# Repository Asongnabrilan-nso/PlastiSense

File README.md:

[Video: PlastiSense Demo](https://youtu.be/B_dy0DAJdtQ)

# PlastiSense

PlastiSense is a precise **filament diameter sensor** powered by the **Seeed Studio XIAO ESP32-C3**. It is designed to monitor filament quality in real-time, offering a web-based dashboard and API for data integration.

## 🚀 Features

-   **Real-time Measurement**: High-precision diameter readings in millimeters (mm).
-   **Web Dashboard**: Hosted on the device itself (`http://winfidel.local`), providing a visual interface for monitoring.
-   **REST API**: JSON endpoints for easy integration with other systems (e.g., OctoPrint, Home Assistant).
-   **WiFi Connectivity**: Connects to your home/office network.
-   **Captive Portal**: Easy initial setup via the `SK-WInFiDEL-Setup` access point.
-   **OTA Updates**: Support for Over-The-Air firmware updates.

## 🛠️ Hardware

The project is built around:
-   **Microcontroller**: [Seeed Studio XIAO ESP32-C3](https://www.seeedstudio.com/Seeed-XIAO-ESP32C3-p-5431.html)
-   **Custom PCB**: Files located in the `PlastiSense_PCB` dictionary.
-   **Stl Files**: 3D printable case files located in `stl` directory.

## 📁 Project Structure

-   `Firmware/`: Source code for the ESP32-C3 firmware (PlatformIO project).
-   `Hardware/`: Mechanical parts and diagrams.
-   `PlastiSense_PCB/`: KiCad PCB design files.
-   `stl/`: 3D printable STL files for the sensing unit.

## ⚡ Getting Started

### 1. Build & Flush Firmware
Detailed instructions for building and flashing the firmware can be found in the [Firmware Documentation](Firmware/README.md).

### 2. Connect to the Device
1.  Power on the PlastiSense device.
2.  Connect to the WiFi network named **SK-WInFiDEL-Setup**.
3.  A captive portal should open. If not, visit `http://192.168.4.1`.
4.  Configure your local WiFi credentials.

### 3. Access the Dashboard
Once connected to your network, access the device at:
-   **URL**: `http://winfidel.local`
-   **API Endpoint**: `http://winfidel.local/api/v0/diameter/read`

For more details on connection and API usage, see the [Connection Guide](Firmware/connection.md).

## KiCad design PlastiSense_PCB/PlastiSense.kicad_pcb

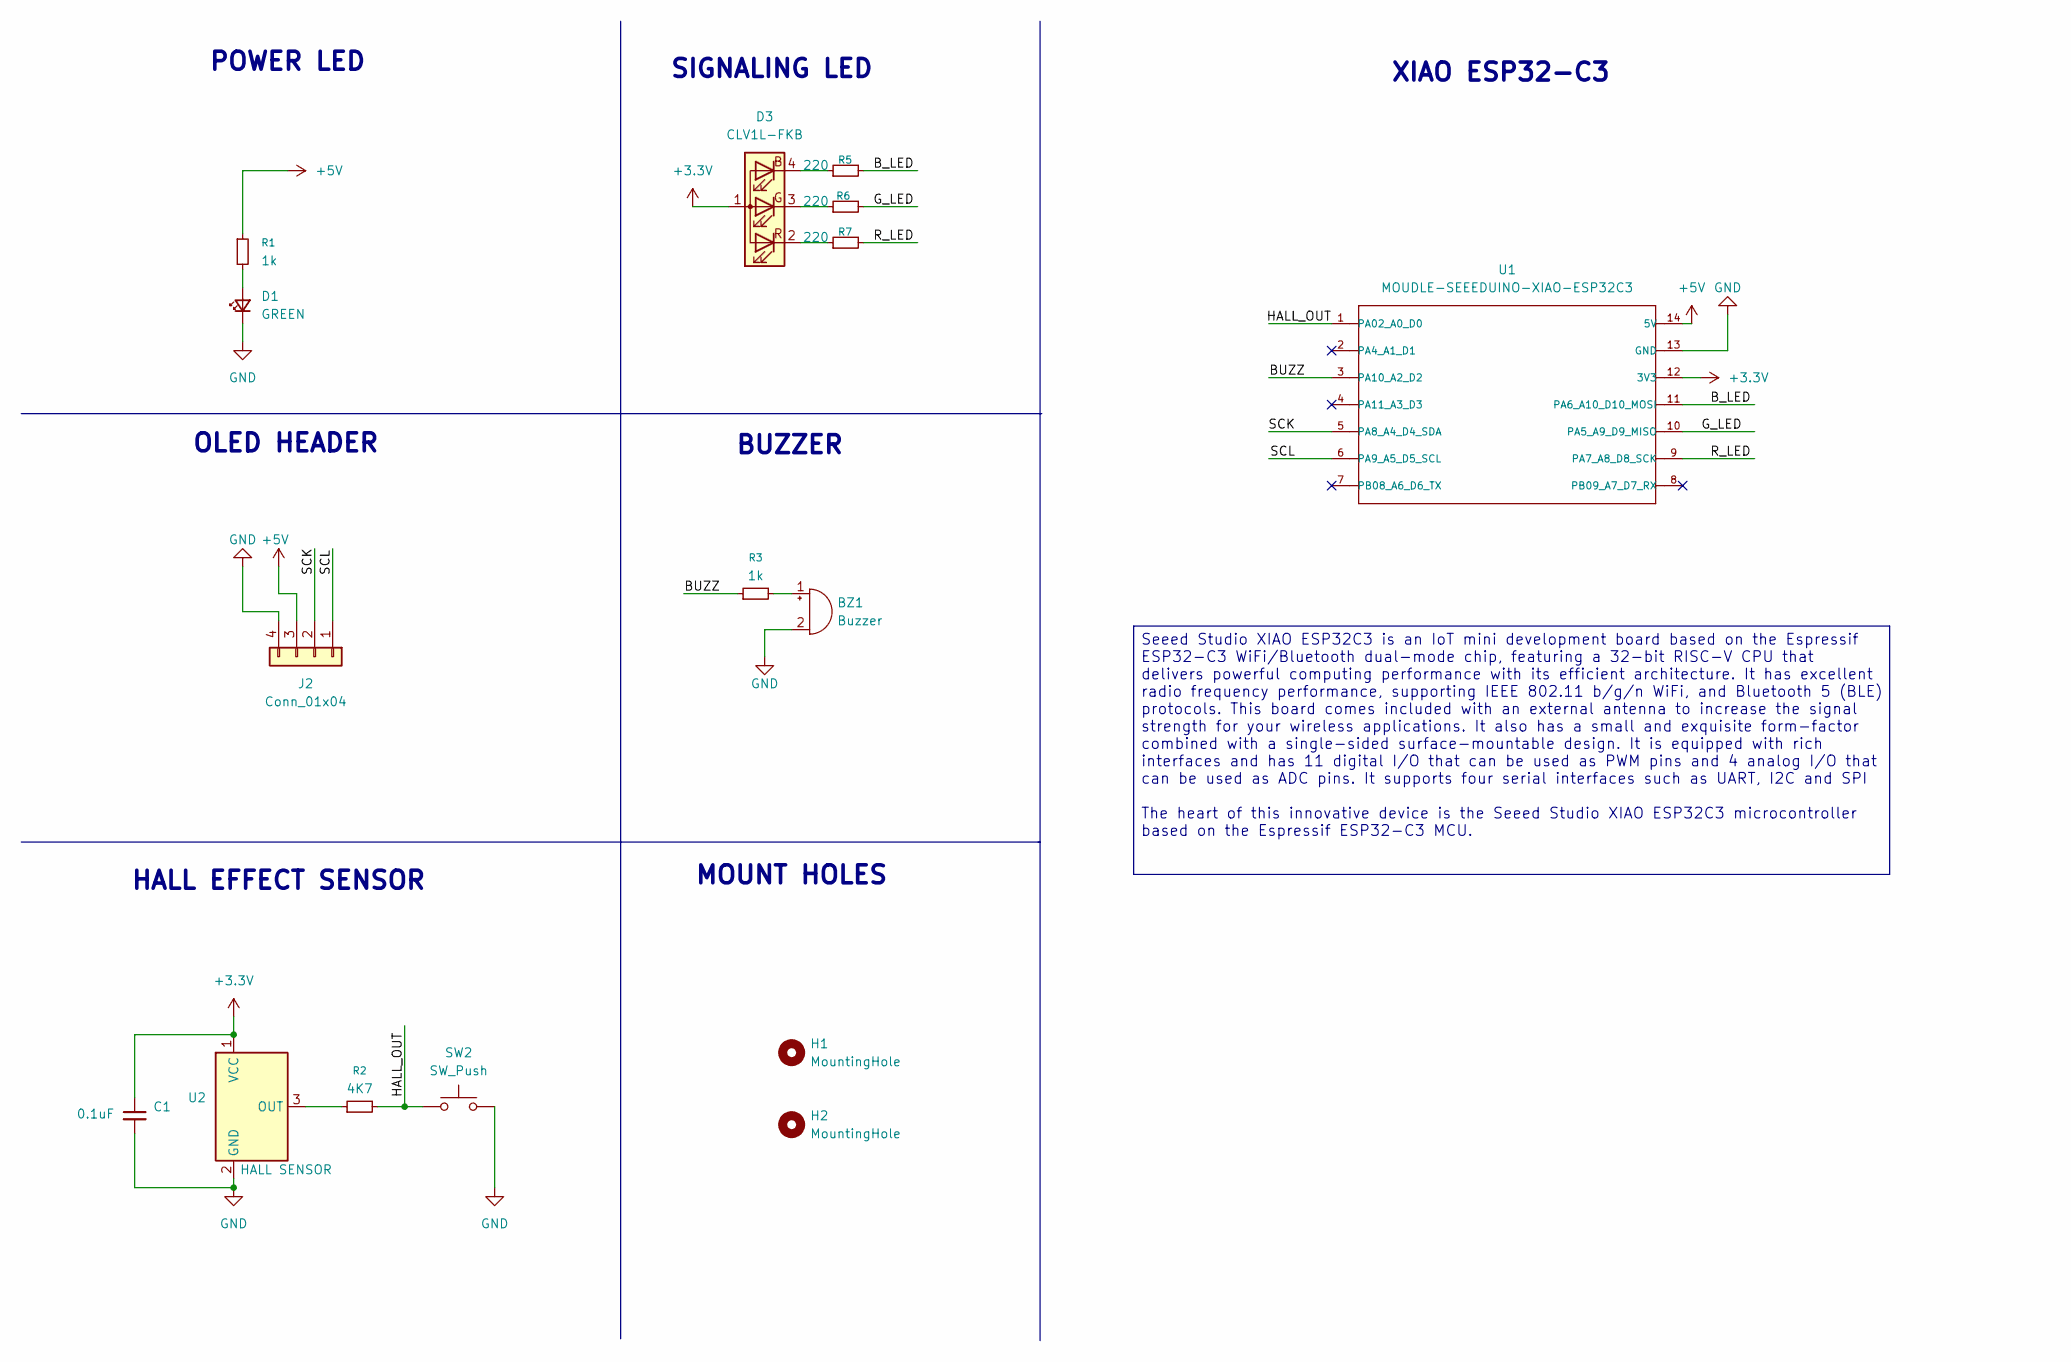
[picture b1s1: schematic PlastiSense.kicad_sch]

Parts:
BZ1: Buzzer; Buzzer_CUI_CPT-9019S-SMT
C1: 0.1uF; C_0504_1310Metric_Pad0.83x1.28mm_HandSolder
D1: GREEN; LED_0201_0603Metric_Pad0.64x0.40mm_HandSolder
D3: CLV1L-FKB; LED_Cree-PLCC4_3.2x2.8mm_CCW
H1, H2: MountingHole; MountingHole_3.2mm_M3
J2: Conn_01x04; PinHeader_1x04_P1.00mm_Vertical
R1, R3: 1k; R_0201_0603Metric_Pad0.64x0.40mm_HandSolder
R2: 4K7; R_0201_0603Metric_Pad0.64x0.40mm_HandSolder
R5, R6, R7: 220; R_0201_0603Metric_Pad0.64x0.40mm_HandSolder
SW2: SW_Push; SW_SPST_B3U-1000P
U1: MOUDLE-SEEEDUINO-XIAO-ESP32C3; MOUDLE14P-SMD-2.54-21X17.8MM
U2: HALL SENSOR; TO-92_Inline

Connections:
+3.3V: C1.1, D3.1 (A), U1.12 (3V3), U2.1 (VCC)
+5V: J2.3, R1.1, U1.14 (5V)
/BUZZ: R3.1, U1.3 (PA10_A2_D2)
/B_LED: R5.2, U1.11 (PA6_A10_D10_MOSI)
/G_LED: R6.2, U1.10 (PA5_A9_D9_MISO)
/HALL_OUT: R2.2, SW2.1, U1.1 (PA02_A0_D0)
/R_LED: R7.2, U1.9 (PA7_A8_D8_SCK)
/SCK: J2.2, U1.5 (PA8_A4_D4_SDA)
/SCL: J2.1, U1.6 (PA9_A5_D5_SCL)
GND: BZ1.2 (-), C1.2, D1.1 (K), J2.4, SW2.2, U1.13 (GND), U2.2 (GND)
unnamed: BZ1.1 (+), R3.2
unnamed: D1.2 (A), R1.2
unnamed: D3.4 (BK), R5.1
unnamed: D3.3 (GK), R6.1
unnamed: D3.2 (RK), R7.1
unnamed: R2.1, U2.3 (OUT)

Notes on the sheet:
MOUNT HOLES
HALL EFFECT SENSOR
OLED HEADER
BUZZER
SIGNALING LED
POWER LED
XIAO ESP32-C3
Seeed Studio XIAO ESP32C3 is an IoT mini development board based on the Espressif ESP32-C3 WiFi/Bluetooth dual-mode chip, featuring a 32-bit RISC-V CPU that delivers powerful computing performance with its efficient architecture. It has excellent radio frequency performance, supporting IEEE 802.11 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

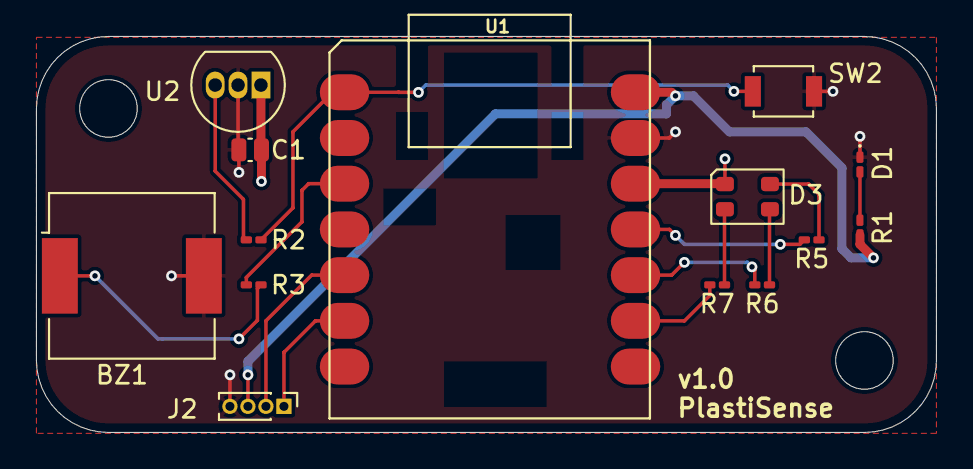
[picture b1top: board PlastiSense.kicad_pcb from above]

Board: 4 copper layers, 50.0 x 22.0 mm, 16 parts (0 on the bottom side), 16 nets.
